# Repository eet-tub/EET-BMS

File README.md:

# EET_BMS 

The EET BMS is an open source battery management system for research and education purposes. It is possible to test new algorithms for state estimation and extend the hardware for more cells. Everything which is needed to rebuild the BMS can be found in this repository. 

## Reading the documentation

We created the documentation in Obsidian. The documentation can also be read in git or in visual studio, but the linking of the screenshot does not work in both of the programs. To see the documentation with the screenshot you have to use obsidian or look at the folder `documentation_res` 

## Tools and programs 

To use the BMS there are different free programs needed. 

| Program             | Description                                                                                                                         |
| ------------------- | ----------------------------------------------------------------------------------------------------------------------------------- |
| KiCad               | for the Hardware schematics                                                                                                         |
| STM32CubeID         | for deploying the BMS project on the STM32 micro controller                                                                         |
| STM32CubeMX         | for deploying the BMS project on the STM32 micro controller and using the ioc file                                                  |
| STM32CubeProgrammer | reading, writing, and verifying device memory. Also used for erasing the flash after a failed deployment of the software and a boot |
| Python              | for the logging script                                                                                                              |

## Repository structure

| folder name    | Description                                                        |
| -------------- | ------------------------------------------------------------------ |
| Firmware       | the BMS firmware for deploying on the BMS                          |
| Hardware       | Hardware schematics                                                |
| Logging_script | python script for the connection of the BMS and a laptop via RS485 |
| docs           | Documentation for deploying, assembling and initialising the BMS   |

## License 

The license information is found in docs/license. There are two licenses. One for the Software which is a MIT license. The second one is for the Hardware, which is CERN Open Hardware Licence.

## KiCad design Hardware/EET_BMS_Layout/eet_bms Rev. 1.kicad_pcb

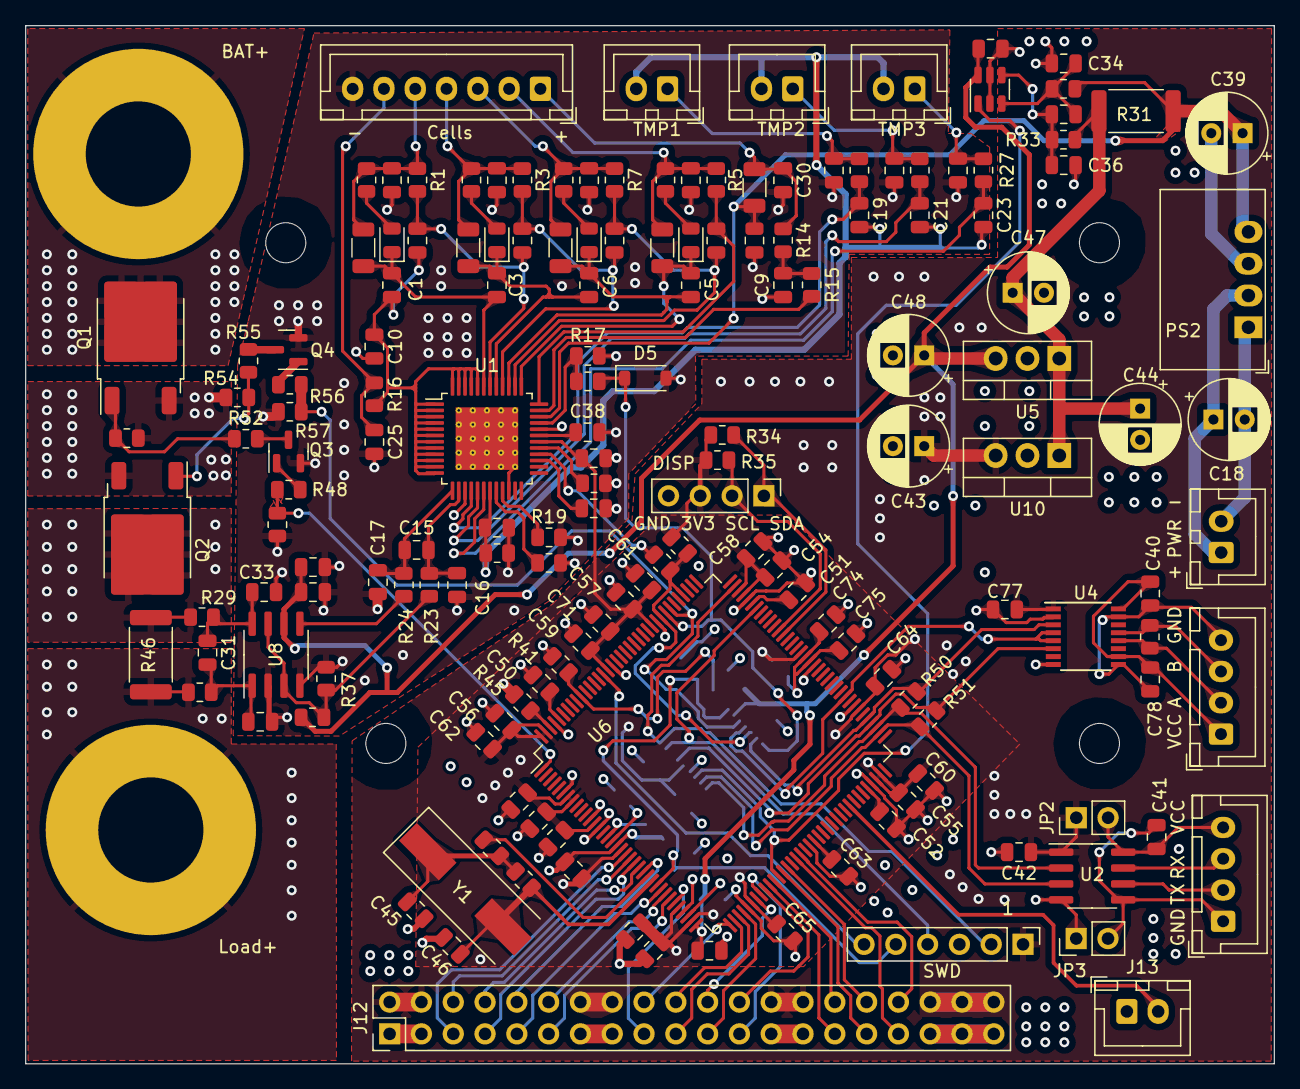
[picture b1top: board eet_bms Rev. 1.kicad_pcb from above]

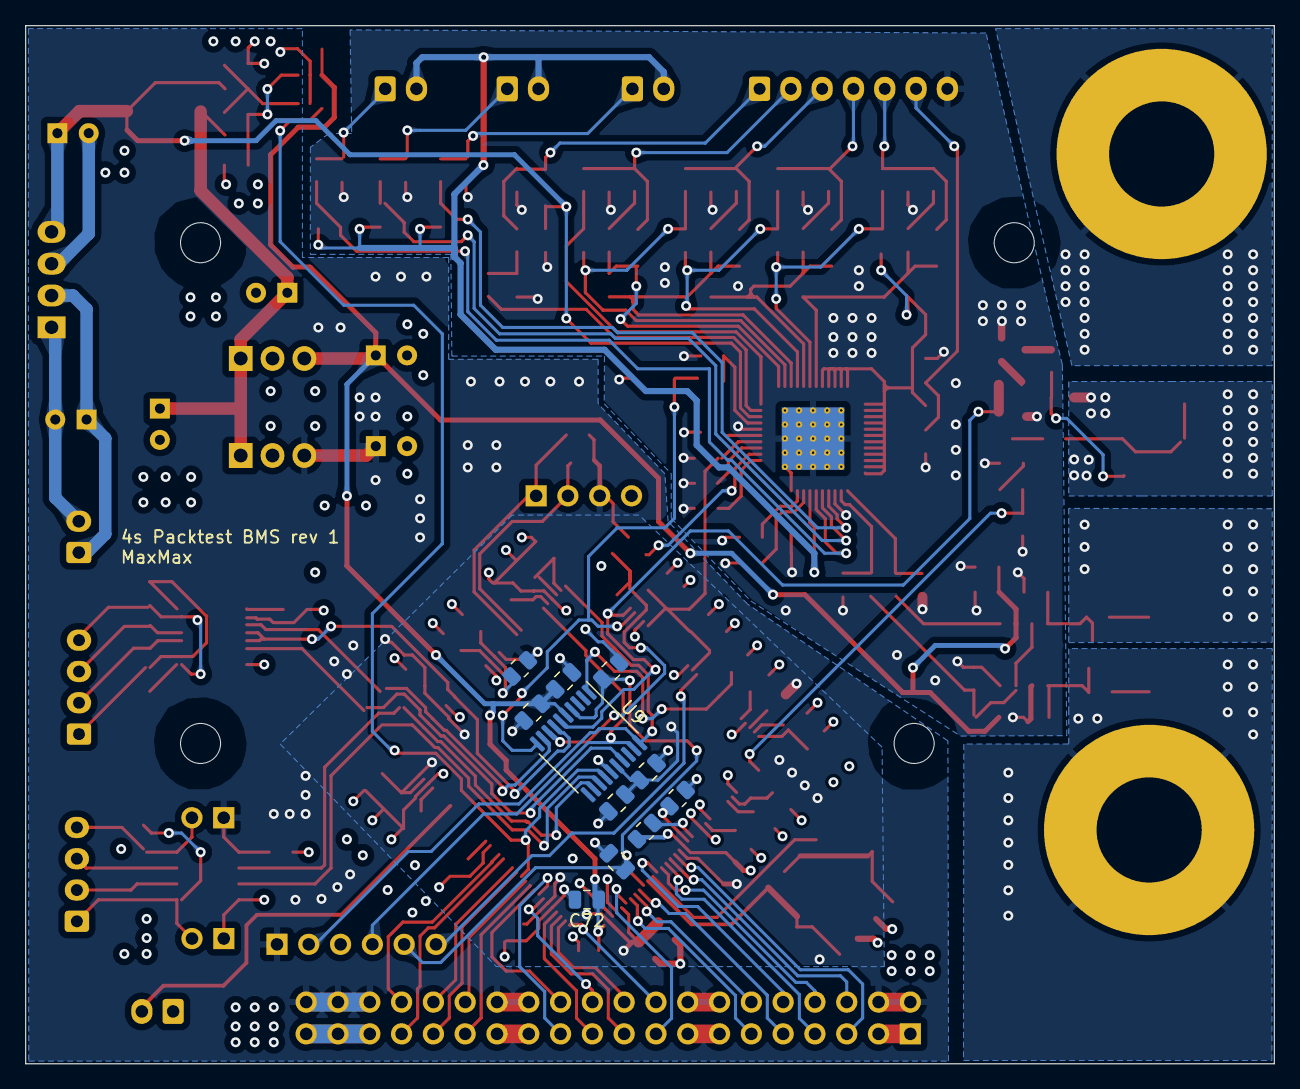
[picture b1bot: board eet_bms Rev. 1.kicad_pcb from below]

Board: 4 copper layers, 99.7 x 82.9 mm, 180 parts (11 on the bottom side), 118 nets.

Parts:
C1, C2, C3, C4, C5, C6, C7, C8, C9, C10, C12, C13, C40, C41, C42, C49, C53, C57, C58, C59, C60, C61, C62, C63, C64, C65, C66, C67, C68, C69, C70, C73, C74, C75, C76, C77, C78, C79, C81, C83, C84: 100n; C_0805_2012Metric
C11, C38: 330n; C_0805_2012Metric
C14, C19, C20, C21, C22, C23, C24: 10n; C_0805_2012Metric
C15, C16, C17, C25, C26, C27, C28, C29, C30, C31, C32, C33, C34, C35, C36: 1n; C_0805_2012Metric
C18, C39, C43, C44, C47, C48: 10uF; CP_Radial_D6.3mm_P2.50mm
C37, C72: 1u; C_0805_2012Metric
C45, C46: 27p; C_0805_2012Metric
C50, C51, C52: 2u2; C_0805_2012Metric
C54, C55, C56, C71, C80, C82: 4u7; C_0805_2012Metric
D1, D2, D3, D4: LED; D_0805_2012Metric
D5: 3V; D_SOD-123
H1, H2, H3, H4: MountingHole; MountingHole_3.2mm_M3
J1: TMP0; JST_XH_B2B-XH-A_1x02_P2.50mm_Vertical
J2: Conn_01x07; JST_XH_B7B-XH-A_1x07_P2.50mm_Vertical
J3: TMP1; JST_XH_B2B-XH-A_1x02_P2.50mm_Vertical
J4: TMP2; JST_XH_B2B-XH-A_1x02_P2.50mm_Vertical
J5: Display; PinHeader_1x04_P2.54mm_Vertical
J6: RS485; JST_XH_B4B-XH-A_1x04_P2.50mm_Vertical
J7: Bat+; MountingHole_8.4mm_M8_Pad
J8: UART_Shell; JST_XH_B4B-XH-A_1x04_P2.50mm_Vertical
J9: Power_In; JST_XH_B2B-XH-A_1x02_P2.50mm_Vertical
J10: SW_Debug_Connector; PinHeader_1x06_P2.54mm_Vertical
J11: Load+; MountingHole_8.4mm_M8_Pad
J12: Conn_02x20_Odd_Even; PinHeader_2x20_P2.54mm_Vertical
J13: PWM; JST_XH_B2B-XH-A_1x02_P2.50mm_Vertical
JP2, JP3: Jumper_2_Open; PinHeader_1x02_P2.54mm_Vertical
PS2: MEE3S0505SC; Converter_DCDC_Murata_MEE3SxxxxSC_THT
Q1, Q2: SUD19P06-60; TO-252-2
Q3, Q4: BSS138; SOT-23
R1, R3, R5, R7, R14, R16: 10; R_0805_2012Metric
R2, R4, R6, R8, R13: 47; R_1206_3216Metric
R9, R10, R11, R12, R37: 470; R_0805_2012Metric
R15: 5R1; R_0805_2012Metric
R17, R18, R19, R21, R41, R47, R49, R54, R57: 33k; R_0805_2012Metric
R20, R28, R34, R35, R36, R45: 1k; R_0805_2012Metric
R22, R23, R24, R25, R26, R27, R32, R33, R38, R48, R52, R53, R55, R56: 100; R_0805_2012Metric
R29, R30, R39, R42, R43, R44, R50, R51: 0; R_0805_2012Metric
R31, R46: 5m; R_2512_6332Metric
R40: R; R_0805_2012Metric
U1: TLE9012DQU; TQFP-48-1EP_7x7mm_P0.5mm_EP5x5mm_ThermalVias
U2: STISO621; SOIC-8_3.9x4.9mm_P1.27mm
U3: INA181; SOT-23-6
U4: ISO1500; SSOP-16_3.9x4.9mm_P0.635mm
U5, U10: LF33_TO220; TO-220-3_Vertical
U6: STM32H755ZITx; LQFP-144_20x20mm_P0.5mm
U8: TSC2012; SOIC-8_3.9x4.9mm_P1.27mm
U9: STM32L031F6Px; TSSOP-20_4.4x6.5mm_P0.65mm
Y1: 16Mhz; Crystal_SMD_HC49-SD

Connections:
+3V3: C12.1, C42.1, C43.1, C53.1, C54.1, C55.1, C56.1, C57.1, C58.1, C59.1, C60.1, C61.1, C62.1, C63.1, C64.1, C65.1, C66.1, C67.1, C68.1, C69.1, C70.1, C71.1, C77.1, C79.1, C82.1, J5.3, J10.1, J12.2, J12.4, J12.14, J12.16, J12.26, J12.28, J12.36, J12.38, J12.40, JP2.1 (A), R20.1, R34.1, R35.1, R44.1, R45.1, U1.30 (VIO), U2.1 (VDD1), U4.1 (VCC1), U6.7 (VDD), U6.8 (VBAT), U6.13 (VDD), U6.19 (VDD), U6.32 (VDD), U6.35 (VREF+), U6.42 (VDD), U6.56 (VDD), U6.70 (VDDLDO), U6.71 (VDD), U6.79 (VDD), U6.92 (VDD), U6.105 (VDDLDO), U6.106 (VDD), U6.119 (VDD), U6.129 (VDD), U6.143 (VDDLDO), U6.144 (VDD), U9.16 (VDD), U10.3 (VO)
/BMS_Frontend/Bat_Current_Sense: R24.2, U8.5 (OUT)
/BMS_Frontend/Current_Sense_Reference: R23.2, R36.2, R37.1, U8.3 (VREF2), U8.7 (VREF1)
/BMS_Frontend/TMP_GND: C14.1, C19.2, C21.2, C23.2, J1.2, J3.2, J4.2, R22.1, U1.19 (TMP_GND)
/BMS_Frontend/UART: R20.2, R53.2, U6.112 (PD0), U6.117 (PD5), U9.8 (PA2)
/Current Sense Amplifier/BAT+: J7.1, Q1.2 (D)
/Current Sense Amplifier/SSR_Junction: Q1.3 (S), Q2.3 (S), R47.1, R54.1
/Current Sense Amplifier/Shunt+: Q2.2 (D), R29.1, R46.1
/Current Sense Amplifier/Shunt-/Load+: J11.1, R30.1, R46.2
/STM_MCU/BOOT0: R41.1, U6.135 (BOOT0), U9.1 (BOOT0)
/STM_MCU/Error: D5.1 (K), R28.2, U6.116 (PD4), U9.10 (PA4)
/STM_MCU/NRST: C49.1, C83.1, J10.5, U6.27 (NRST), U9.4 (NRST)
/STM_MCU/SCL: J5.2, R35.2, U6.97 (PA8)
/STM_MCU/SDA: J5.1, R34.2, U6.96 (PC9)
/STM_MCU/SWCLK: J10.2, U6.107 (PA14), U9.20 (PA14)
/STM_MCU/SWDIO: J10.4, U6.102 (PA13), U9.19 (PA13)
/STM_MCU/SWO: J10.6, U6.130 (PB3)
/STM_MCU/Supply_Current: U3.1, U6.48 (PC5), U9.14 (PB1)
/STM_MCU/TX_Enable: U4.4 (~RE), U4.5 (DE), U6.82 (PD12), U9.7 (PA1)
/STM_MCU/UART1_RX: R50.1, U2.2 (VOA), U6.75 (PB15), U9.12 (PA6)
/STM_MCU/UART1_TX: R51.1, U2.3 (VIB), U6.74 (PB14), U9.13 (PA7)
/STM_MCU/UART3_RX: R50.2, U4.3 (R), U6.77 (PD9), U9.9 (PA3)
/STM_MCU/UART3_TX: R51.2, U4.6 (D), U6.76 (PD8), U9.17 (PA9)
/STM_MCU/VUSB: C74.1, C75.1, R44.2, U6.90 (VDD50_USB), U6.91 (VDD33_USB)
/STM_MCU/XTAL1: R39.1, U6.25 (PH0)
/STM_MCU/XTAL2: C46.1, R40.2, U6.26 (PH1), Y1.2
BAT_Relay_Charge: R56.1, R57.1, U6.115 (PD3), U9.6 (PA0)
BAT_Relay_Discharge: R48.1, R49.1, U6.1 (PE2)
GND: C9.1, C10.2, C11.2, C12.2, C13.2, C14.2, C16.1, C17.2, C20.2, C22.2, C24.2, C25.2, C26.2, C27.2, C28.2, C29.2, C30.2, C32.2, C33.1, C34.1, C36.2, C37.2, C38.2, C39.2, C42.2, C43.2, C44.2, C45.2, C46.2, C47.2, C48.2, C49.2, C50.2, C51.2, C52.2, C53.2, C54.2, C55.2, C56.2, C57.2, C58.2, C59.2, C60.2, C61.2, C62.2, C63.2, C64.2, C65.2, C66.2, C67.2, C68.2, C69.2, C70.2, C71.2, C72.2, C73.2, C74.2, C75.2, C76.2, C77.2, C79.2, C80.2, C81.2, C82.2, C83.2, C84.2, D5.2 (A), J2.7, J5.4, J10.3, J12.1, J12.3, J12.13, J12.15, J12.25, J12.27, J12.35, J12.37, J12.39, J13.1, JP3.1 (A), PS2.3 (-Vout), Q3.2 (S), Q4.2 (S), R17.2, R18.2, R19.2, R21.2, R22.2, R37.2, R41.2, R42.2, R43.1, R49.2, R57.2, U1.15 (GND), U1.22 (GND), U1.32 (NC), U1.49 (GND_PAD), U2.4 (GND1), U3.2 (GND), U3.5 (REF), U4.2 (GND1), U4.8 (GND1), U5.2 (GND), U6.6 (VSS), U6.12 (VSS), U6.14 (VSSSMPS), U6.18 (VSS), U6.33 (VSS), U6.34 (VSSA), U6.41 (VSS), U6.55 (VSS), U6.69 (VSS), U6.80 (VSS), U6.89 (VSS), U6.104 (VSS), U6.118 (VSS), U6.128 (VSS), U6.141 (VSS), U8.2 (GND), U8.4 (SHDN), U9.15 (VSS), U10.2 (GND)
GND2: C41.2, J8.1, JP3.2 (B), U2.5 (GND2)
NTC_A 1: J12.5, U6.20 (PF6)
NTC_A 2: J12.6, U6.21 (PF7)
NTC_A 3: J12.7, U6.22 (PF8)
NTC_A 4: J12.8, U6.23 (PF9)
NTC_A 5: J12.10, U6.24 (PF10)
NTC_A 6: J12.9, U6.28 (PC0)
NTC_A 7: J12.12, U6.29 (PC1)
NTC_A 8: J12.11, U6.30 (PC2_C)
NTC_A 9: J12.17, U6.31 (PC3_C)
NTC_A 10: J12.18, U6.37 (PA0)
NTC_A 11: J12.20, U6.38 (PA1)
NTC_A 12: J12.19, U6.39 (PA2)
NTC_A 13: J12.21, U6.40 (PA3)
NTC_A 14: J12.22, U6.43 (PA4)
NTC_A 15: J12.23, U6.44 (PA5)
NTC_A 16: J12.24, U6.45 (PA6)
NTC_A 17: J12.29, U6.46 (PA7)
NTC_A 18: J12.30, U6.47 (PC4)
NTC_A 19: J12.31, U6.49 (PB0)
NTC_A 20: J12.32, U6.50 (PB1)
NTC_A 21: J12.33, U6.52 (PF11)
NTC_A 22: J12.34, U6.53 (PF14)
unnamed: C9.2, R14.2, R15.1
unnamed: C45.1, R39.2, R40.1, Y1.1
unnamed: C50.1, U6.140 (VCAP)
unnamed: C51.1, U6.103 (VCAP)
unnamed: C52.1, U6.68 (VCAP)
unnamed: D1.2 (A), R9.2
unnamed: C3.1, C6.2, D1.1 (K), R4.2, U1.41 (S10/G9)
unnamed: D2.2 (A), R10.2
unnamed: C1.1, C3.2, D2.1 (K), R2.2, U1.43 (S9/G8)
unnamed: D3.2 (A), R11.2
unnamed: C5.2, C6.1, D3.1 (K), R8.2, U1.39 (S11/G10)
unnamed: D4.2 (A), R12.2
unnamed: C5.1, D4.1 (K), R6.2, U1.37 (S12/G11)
unnamed: C24.1, J1.1, R27.2
unnamed: C30.1, J2.1, R13.1, R14.1
unnamed: C29.1, J2.2, R5.1, R6.1, R12.1
unnamed: C28.1, J2.3, R7.1, R8.1, R11.1
unnamed: C27.1, J2.4, R3.1, R4.1, R9.1
unnamed: C26.1, J2.5, R1.1, R2.1, R10.1
unnamed: C25.1, J2.6, R16.1
unnamed: C22.1, J3.1, R26.2
unnamed: C20.1, J4.1, R25.2
unnamed: C40.1, C78.1, J6.1, U4.10 (VCC2), U4.16 (VCC2)
unnamed: J6.2, R38.2, U4.12 (A)
unnamed: J6.3, R38.1, U4.13 (B)
unnamed: C40.2, C78.2, J6.4, U4.9 (GND2), U4.15 (GND2)
unnamed: J8.2, U2.6 (VOB)
unnamed: J8.3, U2.7 (VIA)
unnamed: C41.1, J8.4, JP2.2 (B), U2.8 (VDD2)
unnamed: C18.1, J9.1, PS2.2 (+Vin)
unnamed: C18.2, J9.2, PS2.1 (-Vin)
unnamed: J13.2, U6.64 (PE14)
unnamed: Q1.1 (G), R47.2, R52.1
unnamed: Q2.1 (G), R54.2, R55.1
unnamed: Q3.3 (D), R52.2
unnamed: Q3.1 (G), R48.2
unnamed: Q4.3 (D), R55.2
unnamed: Q4.1 (G), R56.2
unnamed: C1.2, C2.2, C10.1, R16.2, U1.1 (S6/G5), U1.2 (C5/U5), U1.3 (S5/G4), U1.4 (C4/U4), U1.5 (S4/G3), U1.6 (C3/U3), U1.7 (S3/G2), U1.8 (C2/U2), U1.9 (S2/G1), U1.10 (C1/U1), U1.11 (S1/G0), U1.12 (C0/U0), U1.44 (C8/U8), U1.45 (S8/G7), U1.46 (C7/U7), U1.47 (S7/G6), U1.48 (C6/U6)
unnamed: C2.1, C4.2, R1.2, U1.42 (C9/U9)
unnamed: C4.1, C8.2, R3.2, U1.40 (C10/U10)
unnamed: C7.2, C8.1, R7.2, U1.38 (C11/U11)
unnamed: C7.1, R5.2, U1.36 (C12/U12)
unnamed: R17.1, R28.1, U1.33 (ERR)
unnamed: R53.1, U1.28 (GPIO0/UART_LS)
unnamed: R21.1, U1.29 (GPIO1/UART_HS)
unnamed: R19.1, U1.21 (PWM0/GPIO2)
unnamed: R18.1, U1.20 (PWM1/GPIO3)
unnamed: C23.1, R27.1, U1.18 (TMP0)
unnamed: C21.1, R26.1, U1.17 (TMP1)
unnamed: C19.1, R25.1, U1.16 (TMP2)
unnamed: C15.1, C16.2, R23.1, U1.14 (TMP3)
unnamed: C15.2, C17.1, R24.1, U1.13 (TMP4)
unnamed: R15.2, U1.35 (V+/U12P)
unnamed: C11.1, U1.27 (VDDC)
unnamed: C38.1, U1.31 (VREGOUT(VDDA))
unnamed: C34.2, C35.1, R32.2, U3.3 (+)
unnamed: C35.2, C36.1, R33.2, U3.4 (-)
unnamed: R45.2, U6.142 (PDR_ON)
unnamed: R43.2, U6.16 (VDDSMPS)
unnamed: R42.1, U6.17 (VFBSMPS)
unnamed: C31.1, C33.2, R29.2, U8.8 (IN+)
unnamed: C31.2, C32.1, R30.2, U8.1 (IN-)
unnamed: C44.1, C47.1, R31.2, R33.1, U5.1 (VI), U10.1 (VI)
VDDA: C37.1, C48.1, C72.1, C73.1, C76.1, C80.1, C81.1, C84.1, R36.1, U3.6 (V+), U5.3 (VO), U6.36 (VDDA), U8.6 (VCC), U9.5 (VDDA)
Vext: C13.1, C39.1, PS2.4 (+Vout), R13.2, R31.1, R32.1, U1.34 (VS)

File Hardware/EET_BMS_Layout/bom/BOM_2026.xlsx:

Nr. | References | Value | Footprint | Quantity | For 10x | Orderd | Ordernumber | TME.eu Price |  | Euro
1 | C1, C2, C3, C4, C5, C6, C7, C8, C9, C10, C12, C13, C40, C41, C42, C49, C53, C57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 | 100n | C_0805_2012Metric | 38 | 380 | 400 | CC0805KPX7R9104 | 6.4 |  | 1.07 | https://www.tme.eu/de/details/0805b104k500ct/kondensatoren-m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
2 | C15, C16, C17, C25, C26, C27, C28, C29, C30, C32, C33, C34, C35, C36 | 1n | C_0805_2012Metric | 14 | 140 | 200 | CL21B102KBANNNC | 2.2200000000000002 |  | 0.31 | https://www.tme.eu/de/details/cl21b102kbannnc/kondensatoren-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
3 | C14, C19, C20, C21, C22, C23, C24 | 10n | C_0805_2012Metric | 8 | 80 | 90 | CC0805KRX7R9103 | 2.4 |  | 0.6 | https://www.tme.eu/de/details/cc0805krx7r9103/kondensatoren-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
4 | C18, C39, C43, C44, C47, C48 | 10uF | CP_Radial_D6.3mm_P2.50mm | 6 | 60 | 100 | PF1J100MNN0511U | 2.5099999999999998 |  | 1.1499999999999999 | https://www.tme.eu/de/details/pf1j100mnn0511u/elektrolytisch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 |  |  |  |  |  |  |  | 50Stk
5 | C54, C55, C56, C71 | 4u7 | C_0805_2012Metric | 4 | 40 | 50 | CL21A475KPFNNNG | 0.94 |  | 0.31 | https://www.tme.eu/de/details/cl21a475kpfnnng/kondensatoren-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
6 | C50, C51, C52 | 2u2 | C_0805_2012Metric | 3 | 30 | 50 | CL21B225KAFNNNE | 1.58 |  | 0.28000000000000003 | https://www.tme.eu/de/details/cl21b225kafnnne/kondensatoren-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
7 | C11, C38 | 330n | C_0805_2012Metric | 2 | 20 | 23 | CC0805KKX7R9BB334 | 1.55 |  | 0.15 | https://www.tme.eu/de/details/cc0805kkx7r9bb334/kondensatore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
8 | C37, C72 | 1u | C_0805_2012Metric | 2 | 20 | 23 | CC0805KKX5R8BB105 | 1.0900000000000001 |  | 0.2 | https://www.tme.eu/de/details/cc0805kkx5r8bb105/kondensatore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
9 | C45, C46 | 27p | C_0805_2012Metric | 2 | 20 | 23 | C0805C270J5GAC | 0.91 |  | 7.0000000000000007E-2 | https://www.tme.eu/de/details/c0805c270j5gac/kondensatoren-m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
10 | R22, R23, R24, R25, R26, R27, R29, R30, R32, R33, R48, R52, R53 | 100 | R_0805_2012Metric | 13 | 130 | 140 | CRG0805F100R | 1.33 |  | 0.16 | https://www.tme.eu/de/details/crg0805f100r/smd-widerstande/t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
11 | R20, R28, R34, R35, R36, R45, R47 | 1k | R_0805_2012Metric | 7 | 70 | 100 | CRCW08051K00FKTABC | 1.66 |  | 0.05 | https://www.tme.eu/de/details/crcw08051k00fktabc/smd-widerst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
12 | R1, R3, R5, R7, R14, R16 | 10 | R_0805_2012Metric | 6 | 60 | 100 | CRCW080510R0FKTABC | 1.64 |  | 0.04 | https://www.tme.eu/de/details/crcw080510r0fktabc/smd-widerst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
13 | R2, R4, R6, R8, R13 | 47 | R_1206_3216Metric | 5 | 50 | 100 | HP06-47R1% | 2.95 |  | 2.69 | https://www.tme.eu/de/details/hp06-47r1%25/smd-widerstande/r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 |  |  |  |  |  |  |  | 100
14 | R9, R10, R11, R12, R37 | 470 | R_0805_2012Metric | 5 | 50 | 100 | SMD0805-470R-1% | 1.46 |  | 1.33 | https://www.tme.eu/de/details/smd0805-470r-1%25/smd-widersta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 |  |  |  |  |  |  |  | 100
15 | R17, R18, R19, R21, R49 | 33k | R_0805_2012Metric | 5 | 50 | 100 | SMD0805-33K-1% | 1.55 |  | 1.42 | https://www.tme.eu/de/details/smd0805-33k-1%25/smd-widerstan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 |  |  |  |  |  |  |  | 100
16 | R42, R43, R44 | 0 | R_0805_2012Metric | 4 | 40 | 100 | CRCW08050000Z0TABC | 1.1399999999999999 |  | 0.03 | https://www.tme.eu/de/details/crcw08050000z0tabc/smd-widerst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
17 | R31, R46 | 5m | R_2512_6332Metric | 2 | 20 | 25 | MAR251202FR005 | 1.62 |  | 0.8 | https://www.tme.eu/de/details/mar251202fr005s/smd-widerstand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 |  |  |  |  |  |  |  | 5 | MAR251202FR005S
19 | R15 | 5R1 | R_0805_2012Metric | 1 | 10 | 20 | ERJ6GEYJ5R1V | 0.43 |  | 0.05 | https://www.tme.eu/de/details/erj6geyj5r1v/smd-widerstande/p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
20 | R41 | 10k | R_0805_2012Metric | 1 | 10 | 20 | ERJ6ENF1002V | 0.74 |  | 0.02 | https://www.tme.eu/de/details/erj6enf1002v/smd-widerstande/p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
21 | D1, D2, D3, D4 | LED | D_0805_2012Metric | 4 | 40 | 50 | FYLS-0805PGC | 1.7 |  | 0.51 | https://www.tme.eu/de/details/fyls-0805pgc/led-dioden-smd-bu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 |  |  |  |  |  |  |  | 10
22 | D5 Diode | 3V | D_SOD-123 | 1 | 10 | 25 | MMSZ4683-TP | 0.74 |  | 0.08 | https://www.tme.eu/de/details/mmsz4683-tp/zener-dioden-smd/m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
24 | U5, U10 | LF33_TO220 | TO-220-3_Vertical | 2 | 20 | 20 | LF33CV | 16.899999999999999 |  | 1.81 | https://www.tme.eu/de/details/lf33cv/ldo-festspannungsregler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
25 | U1 | TLE9012DQU | TQFP-48-1EP_7x7mm_P0.5mm_EP5x5mm | 1 | 10 | 10 | sponsert | ------- |  | 5.8904999999999994 | https://www.infineon.com/part/tle9012dqu |  |  |  |  |  |  |  |  | Dollar
26 | U2 | STISO621 | SOIC-8_3.9x4.9mm_P1.27mm | 1 | 10 | 10 | ADUM1200ARZ | 15.5 |  | 2.21 | https://www.tme.eu/de/details/adum1200arz/integ-schalt-sonst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
28 | U4 | ISO1500 | SSOP-16_3.9x4.9mm_P0.635mm | 1 | 10 | 10 | THVD1500D | 14.9 |  | 1.1000000000000001 | https://www.tme.eu/de/details/thvd1500d/integ-schalt-rs232-r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
29 | U6 | STM32H755ZITx | LQFP-144_20x20mm_P0.5mm | 1 | 10 | 10 | sponsert | ------- |  | 15.214999999999998 | https://estore.st.com/en/stm32h755zit6-cpn.html |  |  |  |  |  |  |  |  | Dollar
30 | U8 | TSC2012 | SOIC-8_3.9x4.9mm_P1.27mm | 1 | 10 | 13 | TSC2012IDT | 12.7 |  | 1.94 | https://www.mouser.de/ProductDetail/STMicroelectronics/TSC20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
32 | Y1 | Crystal | Crystal_SMD_HC49-SD | 1 | 10 | 10 | 16.00M-SMDHC49S | 2.35 |  | 0.8 | https://www.tme.eu/de/details/16.00m-smdhc49s/quarzresonator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 |  |  |  |  |  |  |  | 2
34 | Q1, Q2 | SUD19P06-60 | TO-252-2 | 2 | 20 | 20 | SUD19P06-60-GE3 | 15.86 |  | 1.75 | https://www.tme.eu/de/details/sud19p06-60-ge3/p-kanal-transi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
35 | PS2 | MEE3S0505SC | 3W DCDC Murata getauscht gegen kleinere 1W Variante | 1 | 10 | 10 | RFM-0505S | 16.399999999999999 |  | 1.64 | https://www.tme.eu/de/details/rfm-0505s/dc-dc-wandler/recom/
36 | Q3 | BSS138 | SOT-23 | 2 | 20 | 25 | BSS138A-TP | 0.55000000000000004 |  | 0.18 | https://www.tme.eu/de/details/bss138a-tp/n-kanal-transistore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
37 | J1, J3, J4, J9 | TMP0, TMP1, TMP2 | JST_XH_B2B-XH-A_1x02_P2.50mm_Vertical | 4 | 40 | 50 | B2B-XH-A | 5 |  | 0.3 | https://www.tme.eu/de/details/b2b-xh-a/signalsteckverbinder-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
38 | J2 | Conn_01x07 | JST_XH_B7B-XH-A_1x07_P2.50mm_Vertical | 1 | 10 | 11 | B7B-XH-A | 3.42 |  | 0.19 | https://www.tme.eu/de/details/b7b-xh-a/signalsteckverbinder-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
41 | J5 | Conn_01x04 | PinHeader_1x04_P2.54mm_Vertical | 1 | 10 | 10 | ZL262-4SG | 0.72 |  | 0.66 | https://www.tme.eu/de/details/zl262-4sg/stiftleisten-und-buc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 |  |  |  |  |  |  |  | 10
42 | J6, J8 | RS485 | JST_XH_B4B-XH-A_1x04_P2.50mm_Vertical | 2 | 20 | 21 | B4B-XH-A | 3.49 |  | 0.22 | https://www.tme.eu/de/details/b4b-xh-a/signalsteckverbinder-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 |  |  |  |  |  |  |  | 2
46 | J10, J12 | SW_Debug_Connector | PinHeader_2x20_P2.54mm_Vertical | 2.5 | 25 | 30 | ZL202-40G | 8.91 |  | 2.95 | https://www.tme.eu/de/details/zl202-40g/stiftleisten-und-buc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 |  |  |  |  |  |  |  | 10
48 | J13 |  | PinHeader_2x20_P2.54mm_Vertical | 2 | 20 | 22 | ZL262-40DG | 6.78 |  | 0.77 | https://www.tme.eu/de/details/zl262-40dg/stiftleisten-und-bu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
 |  |  |  |  |  |  |  | 160.04000000000002 |  | 48.945499999999988

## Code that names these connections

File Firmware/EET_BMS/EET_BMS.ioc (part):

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Mcu.Name=STM32H755ZITx
Mcu.Package=LQFP144
Mcu.UserName=STM32H755ZITx
PA0.GPIOParameters=PinAttribute
PA0.Mode=Asynchronous
PA0.PinAttribute=CortexM4
PA0.Signal=UART4_TX
PA13\ (JTMS/SWDIO).GPIOParameters=PinAttribute
PA13\ (JTMS/SWDIO).Mode=Serial_Wire
PA13\ (JTMS/SWDIO).PinAttribute=CortexM7
PA13\ (JTMS/SWDIO).Signal=DEBUG_JTMS-SWDIO
PA14\ (JTCK/SWCLK).GPIOParameters=PinAttribute
PA14\ (JTCK/SWCLK).Mode=Serial_Wire
PA14\ (JTCK/SWCLK).PinAttribute=CortexM7
PA14\ (JTCK/SWCLK).Signal=DEBUG_JTCK-SWCLK
PA8.GPIOParameters=PinAttribute
PA8.Mode=I2C
PA8.PinAttribute=CortexM7
PA8.Signal=I2C3_SCL
PB14.GPIOParameters=PinAttribute
PB14.Mode=Asynchronous
PB14.PinAttribute=CortexM7
PB14.Signal=USART1_TX
PB15.GPIOParameters=PinAttribute
PB15.Mode=Asynchronous
PB15.PinAttribute=CortexM7
PB15.Signal=USART1_RX
PC9.GPIOParameters=PinAttribute
PC9.Mode=I2C
PC9.PinAttribute=CortexM7
PC9.Signal=I2C3_SDA
PD0.GPIOParameters=PinAttribute
PD0.Mode=Asynchronous
PD0.PinAttribute=CortexM4
PD0.Signal=UART4_RX
PD12.GPIOParameters=PinAttribute
PD12.Mode=Hardware Flow Control (RS485)
PD12.PinAttribute=CortexM4
PD12.Signal=USART3_DE
PD3.ContextOwner=CortexM4
PD3.GPIOParameters=GPIO_Label,PinAttribute
PD3.GPIO_Label=BAT_Charge
PD3.PinAttribute=CortexM4
PD3.Signal=GPIO_Output
PD4.ContextOwner=CortexM4
PD4.GPIOParameters=GPIO_Label,PinAttribute
PD4.GPIO_Label=TLE_Error
PD4.PinAttribute=CortexM4
PD4.Signal=GPIO_Input
PD5.GPIOParameters=PinAttribute
PD5.Mode=Half_duplex(single_wire_mode)
PD5.PinAttribute=CortexM4
PD5.Signal=USART2_TX
PD8.GPIOParameters=PinAttribute
PD8.Mode=Asynchronous
PD8.PinAttribute=CortexM4
PD8.Signal=USART3_TX
PD9.GPIOParameters=PinAttribute
PD9.Mode=Asynchronous
PD9.PinAttribute=CortexM4
PD9.Signal=USART3_RX
PE2.ContextOwner=CortexM4
PE2.GPIOParameters=GPIO_Label,PinAttribute
PE2.GPIO_Label=BAT_Discharge
PE2.PinAttribute=CortexM4
PE2.Signal=GPIO_Output
RCC.HSE_VALUE=16000000
RCC.SYSCLKFreq_VALUE=128000000
RCC.SYSCLKSource=RCC_SYSCLKSOURCE_PLLCLK
board=custom

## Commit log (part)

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2026-04-20 Adding BMS
2026-04-20 filled the README.md
2026-04-20 edit readme
2026-04-22 deleted release folder and added docu
2026-04-27 added docs
2026-04-29 added sfinx documentation
2026-04-30 deleting sphinx and starting from scratch
2026-05-05 adding sphinx again
2026-05-05 Add GitHub Actions workflow for documentation build
2026-05-06 updated safety
2026-05-06 deleted git hub pages
2026-05-06 renamed folder
2026-05-06 Add documentation workflow for GitHub Pages
    Set up a GitHub Actions workflow for documentation generation and deployment to GitHub Pages.
2026-05-07 moved conf.py
2026-05-07 Refactor GitHub Actions workflow for documentation
2026-05-07 renamed folder docs
2026-05-07 refactor yml data
2026-05-07 git hub page
2026-05-07 new test gh-pages
2026-05-07 changes in docs
2026-05-08 fixed a bug in the firmware. Added in Hardware documentation
2026-05-11 hopefully fix from build of the project in STM32CubeIDE
2026-05-11 changed license for hardware. Is the same for documentation
2026-05-11 changes in license
2026-05-11 deploy: 2d8e5f7b9735457beb4165a3ee6bab54836362e0
2026-05-28 update license and docs
2026-06-12 Update TLE_LL_Driver.c
    huart RX byte cleaning added
2026-06-23 Overcurrent Protection
    safety test for overcurrent protection. Code is changed because while applying over current, MOSFET goes on and off all the time and it looks like "pwm signal" and current couldn't completly cut
2026-06-26 Overvoltage protection
    as in the previous code of the overcurrent, overvoltage mosfet gate keeps on/off like PWM signal. Changed the code with the same logic of the overcurrent working principle
